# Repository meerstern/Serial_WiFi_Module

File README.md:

# Serial_WiFi_Module
 AMW037 module board

## 告知
  * メーカ側でAMW037の生産終了が告知されたため、在庫限りです  
  * 次ロットの生産予定はありません  
  * 新規開発の採用には適しません  

## 概要 
  * SiliconLabs製WiFiモジュールAMW037を搭載した変換基板です。  
  * WiFi制御ソフトウェアが予め書き込まれているため、容易にWiFi通信を使⽤することができます。
  * 3.3Vシリアル通信(UART,初期115200bps)で外部機器からパラメータを設定することが可能です。  
  * 3.3Vシリアル通信はGROVEコネクタでも接続できます。
  * 基板上からAMW037のすべてのIOにアクセスできます。
  * TELEC(技適)認証済 [工事設計認証番号 201-180092][3] 
  
## 注意 
  * 正常に起動するためには電源投入時にUART_TX=GND、IO_2=VDD、IO_3=VDDである必要があります。  
  * UARTポートと干渉して正常に起動できない場合はUART_TXとGNDにプルダウン抵抗(5k~10k)を追加してください。  
  * なお、モジュール内部でUART_TX=GND、IO_2=VDD、IO_3=VDDになるようにプルダウン抵抗及びプルアップ抵抗が実装されています。  

## 関連情報
  * [データシート][1]
  * [製品紹介サイト][2]
 
## 販売サイト
  * [スイッチサイエンス][4]
 
[1]: https://www.silabs.com/documents/login/data-sheets/ADS-MW037-ZentriOS-101R.pdf "*1"
[2]: https://jp.silabs.com/products/wireless/wi-fi/zentri-wi-fi-modules/amw037-wifi-module "*2"
[3]: https://www.tele.soumu.go.jp/giteki/SearchServlet?pageID=jg01_01&PC=201&TC=N&PK=1&FN=181025N201&SN=%94F%8F%D8&LN=213&R1=*****&R2=***** "*3"
[4]: https://www.switch-science.com/products/5795

MIT Lisense

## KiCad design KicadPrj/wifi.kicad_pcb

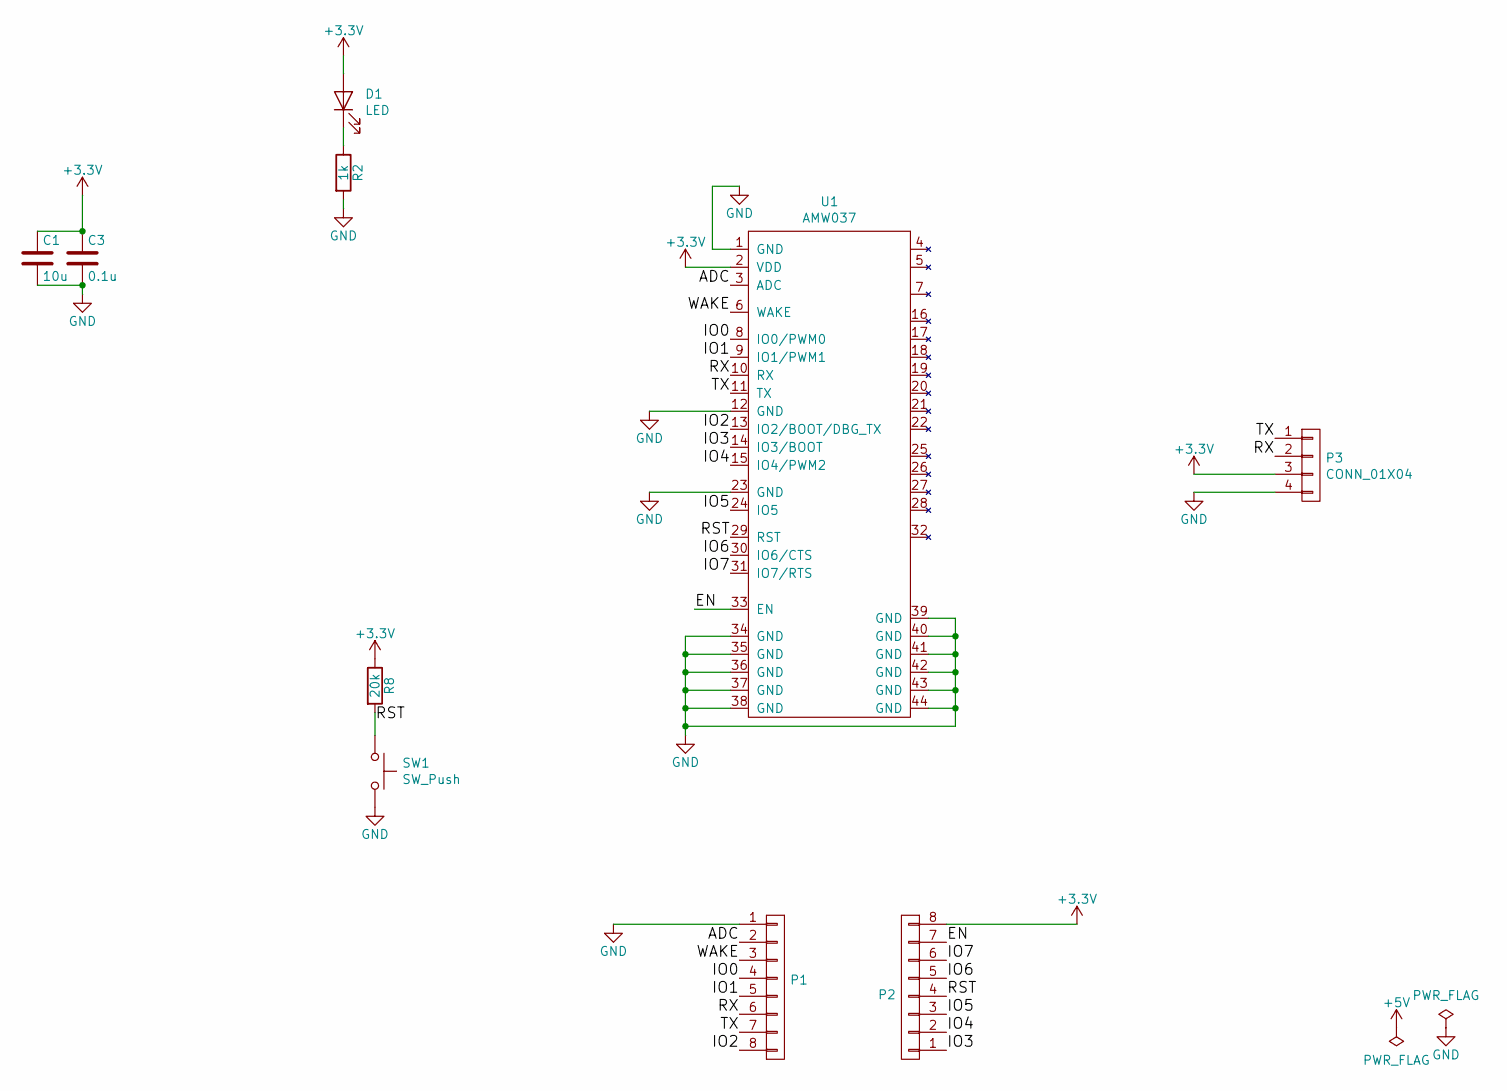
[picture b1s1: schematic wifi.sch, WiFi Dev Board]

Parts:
C1: 10u; C_0805_2012Metric
C3: 0.1u; C_0603_1608Metric
D1: LED; generic-LED1608
P1, P2: CONN_01X08; pinhead-1X08
P3: CONN_01X04; GROVE
R2: 1k; R_0603_1608Metric
R8: 20k; R_0603_1608Metric
SW1: SW_Push; SKRPACE010
U1: AMW037

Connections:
+3V3: C1.1, C3.1, D1.A, P2.8, P3.3, R8.1, U1.2 (VDD)
/ADC: P1.2, U1.3 (ADC)
/EN: P2.7, U1.33 (EN)
/IO0: P1.4, U1.8 (IO0/PWM0)
/IO1: P1.5, U1.9 (IO1/PWM1)
/IO2: P1.8, U1.13 (IO2/BOOT/DBG_TX)
/IO3: P2.1, U1.14 (IO3/BOOT)
/IO4: P2.2, U1.15 (IO4/PWM2)
/IO5: P2.3, U1.24 (IO5)
/IO6: P2.5, U1.30 (IO6/CTS)
/IO7: P2.6, U1.31 (IO7/RTS)
/RST: P2.4, R8.2, SW1.1, U1.29 (RST)
/RX: P1.6, P3.2, U1.10 (RX)
/TX: P1.7, P3.1, U1.11 (TX)
/WAKE: P1.3, U1.6 (WAKE)
GND: C1.2, C3.2, P1.1, P3.4, R2.2, SW1.2, U1.1 (GND), U1.12 (GND), U1.23 (GND), U1.34 (GND), U1.35 (GND), U1.36 (GND), U1.37 (GND), U1.38 (GND), U1.39 (GND), U1.40 (GND), U1.41 (GND), U1.42 (GND), U1.43 (GND), U1.44 (GND)
unnamed: D1.K, R2.1

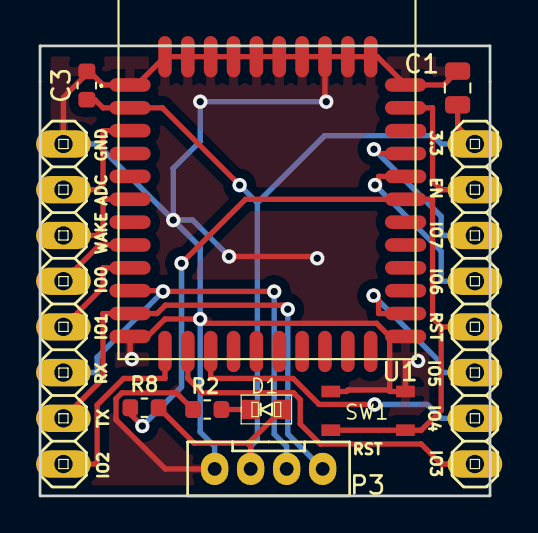
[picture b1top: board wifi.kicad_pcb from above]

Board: 2 copper layers, 25.0 x 25.0 mm, 10 parts (0 on the bottom side), 17 nets.

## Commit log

2019-06-28 Upload the kicad project
2019-07-06 Add README
2019-07-13 Add images
2019-07-31 Add PDF Data
2022-12-06 Add shop link
